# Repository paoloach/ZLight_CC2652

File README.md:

# ZLight_CC2652
A light and a PIR handled by Zigbee

The firmware is made for a CC2652RB and CC2652P TI chips and it is avaiable under the firmware folder.
The first version was for E72-2G4M05S1F (CC2652RB) module but for his shortage, I migrated to the E72-2G4M05S1E module, based on CC2652P1F chip.

For licence issue, I can't put the sources, but you can request at me (pachdjian@gmail.com)

Into firmware folder there are both the firmware.
Into Box, there is a Freecad model for a box I made
Into Schematic thare is two versions on a KiCad circuit with a PCB layout. 
 * The first version is for a E72-2G4M05S1F and it is without a PIR connector.
 * The second version is for a E72-2G4M05S1E module, it contains some fixes and enanchements 

# Instruction

The power supply is 12 Volts. The maximum limits is set by the LM1117 chip that has a maximum input value of 15 Volts.
The PIR used is a AS312, but there are a plenty of others PIR sensors. The important thing is that it should be power by 3.3 volt and a digital output.

The consume is about 0.4 - 0.5 A, so the maximum  emitted light is about 5-6 Watt.
It implement a On/Off and Controll cluster, so you can reduce the luminosity.

The first time the ZLight start it search for a available network.
The two leds blink alternately.

If you need to reset the network, press button 1 for more that 5 seconds.

Then the ZLight will be reset the network configuration and it will begin to search for a new network, blinking the two leds

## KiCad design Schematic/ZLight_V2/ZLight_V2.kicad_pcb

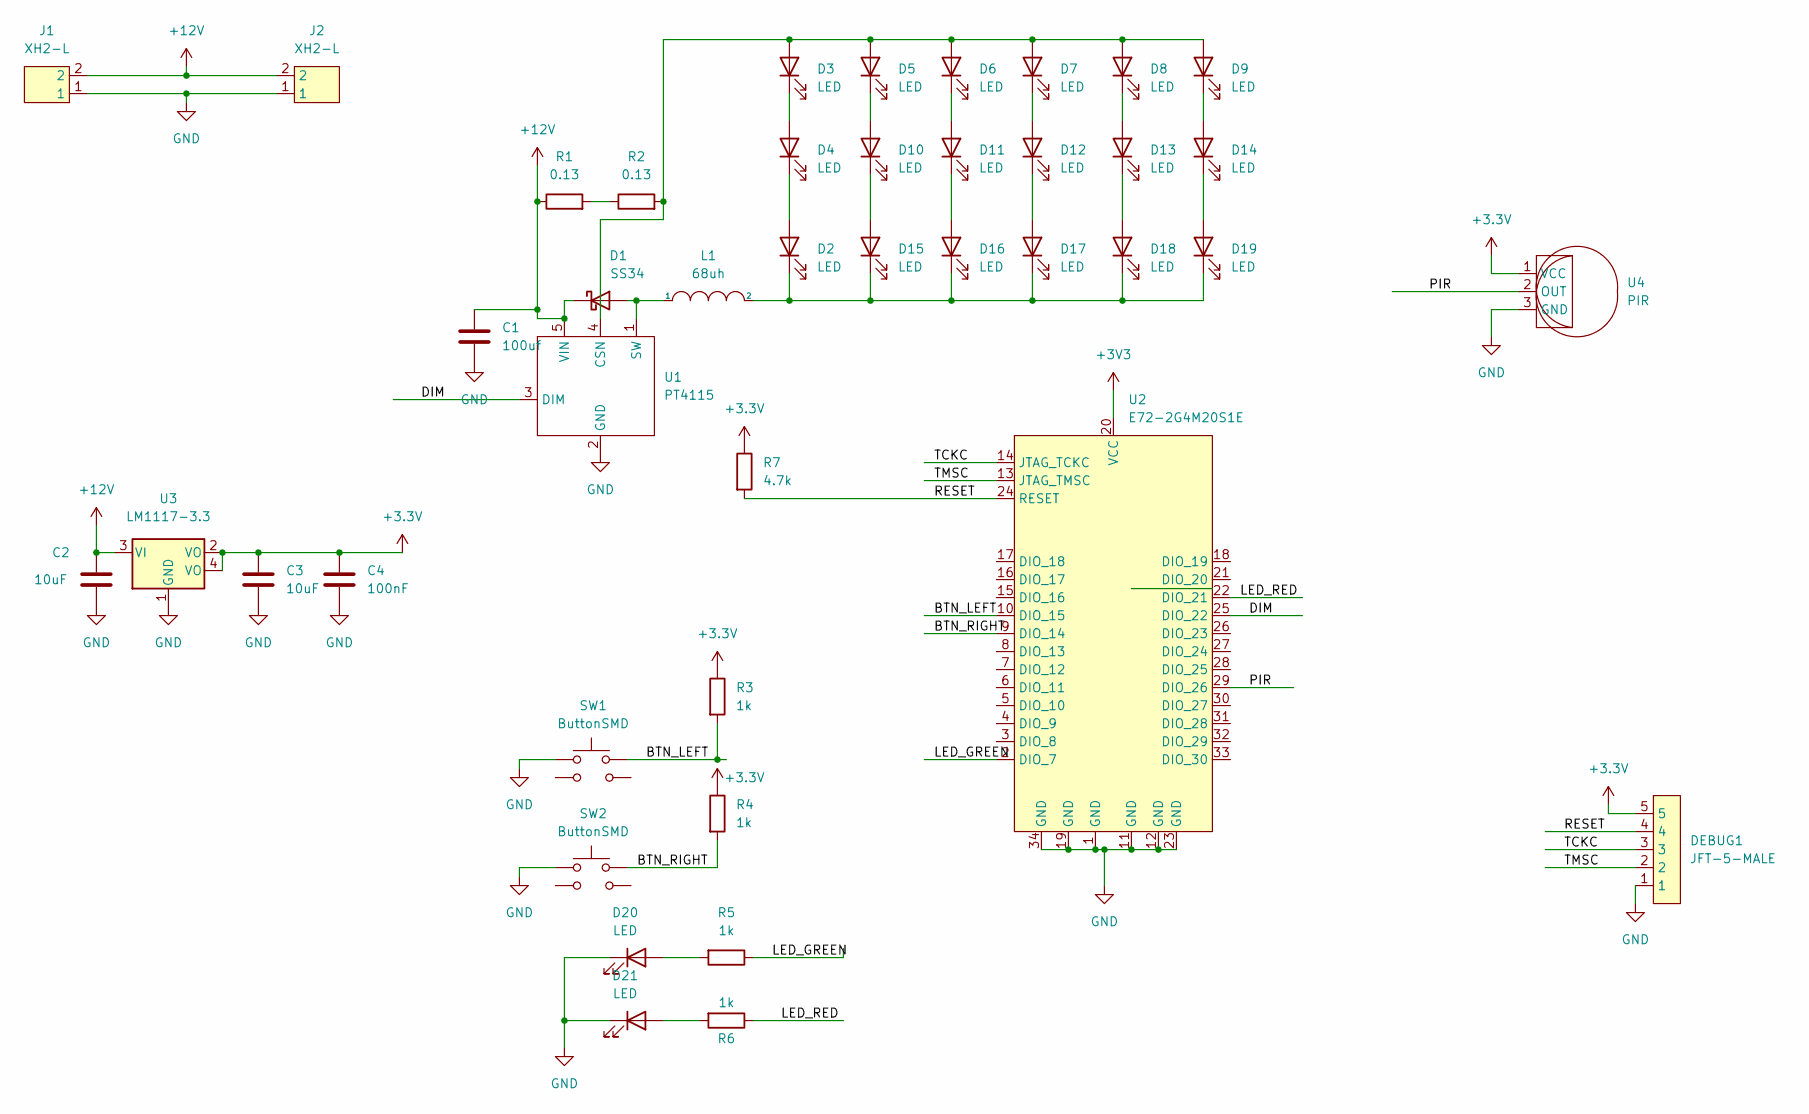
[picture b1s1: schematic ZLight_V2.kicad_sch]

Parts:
C1: 100uf; C_1210_3225Metric_Pad1.33x2.70mm_HandSolder
C2, C3: 10uF; C_0603_1608Metric_Pad1.08x0.95mm_HandSolder
C4: 100nF; C_0603_1608Metric_Pad1.08x0.95mm_HandSolder
D1: SS34
D2, D3, D4, D5, D6, D7, D8, D9, D10, D11, D12, D13, D14, D15, D16, D17, D18, D19: LED; LED_Yuji_5730
D20, D21: LED; LED_0603_1608Metric_Pad1.05x0.95mm_HandSolder
DEBUG1: JFT-5-MALE; XH5-V
J1, J2: XH2-L; XH2-H
L1: 68uh; RH127
R1, R2: 0.13; R_0603_1608Metric_Pad0.98x0.95mm_HandSolder
R3, R4, R5, R6: 1k; R_0603_1608Metric_Pad0.98x0.95mm_HandSolder
R7: 4.7k; R_0603_1608Metric_Pad0.98x0.95mm_HandSolder
SW1, SW2: ButtonSMD
U1: PT4115; SOT-89-5_Handsoldering
U2: E72-2G4M20S1E
U3: LM1117-3.3; SOT-223
U4: PIR; XH3-V

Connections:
+12V: C1.1, C2.1, D1.1 (K), J1.2, J2.2, R1.1, U1.5 (VIN), U3.3 (VI)
/BTN_LEFT: R3.2, SW1.2, U2.10 (DIO_15)
/BTN_RIGHT: R4.2, SW2.2, U2.9 (DIO_14)
/DIM: U1.3 (DIM), U2.25 (DIO_22)
/LED_GREEN: R5.1, U2.2 (DIO_7)
/LED_RED: R6.1, U2.22 (DIO_21)
/PIR: U2.29 (DIO_26), U4.2 (OUT)
/RESET: DEBUG1.4, R7.2, U2.24 (RESET)
/TCKC: DEBUG1.3, U2.14 (JTAG_TCKC)
/TMSC: DEBUG1.2, U2.13 (JTAG_TMSC)
GND: C1.2, C2.2, C3.2, C4.2, D20.1 (K), D21.1 (K), DEBUG1.1, J1.1, J2.1, SW1.1, SW2.1, U1.2 (GND), U2.1 (GND), U2.11 (GND), U2.12 (GND), U2.19 (GND), U2.23 (GND), U2.34 (GND), U3.1 (GND), U4.3 (GND)
unnamed: D1.2 (A), L1.1, U1.1 (SW)
unnamed: D2.2 (A), D4.1 (K)
unnamed: D3.1 (K), D4.2 (A)
unnamed: D3.2 (A), D5.2 (A), D6.2 (A), D7.2 (A), D8.2 (A), D9.2 (A), R2.2, U1.4 (CSN)
unnamed: D10.1 (K), D15.2 (A)
unnamed: D5.1 (K), D10.2 (A)
unnamed: D11.1 (K), D16.2 (A)
unnamed: D6.1 (K), D11.2 (A)
unnamed: D12.1 (K), D17.2 (A)
unnamed: D7.1 (K), D12.2 (A)
unnamed: D13.1 (K), D18.2 (A)
unnamed: D8.1 (K), D13.2 (A)
unnamed: D14.1 (K), D19.2 (A)
unnamed: D9.1 (K), D14.2 (A)
unnamed: D2.1 (K), D15.1 (K), D16.1 (K), D17.1 (K), D18.1 (K), D19.1 (K), L1.2
unnamed: D20.2 (A), R5.2
unnamed: D21.2 (A), R6.2
unnamed: R1.2, R2.1

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
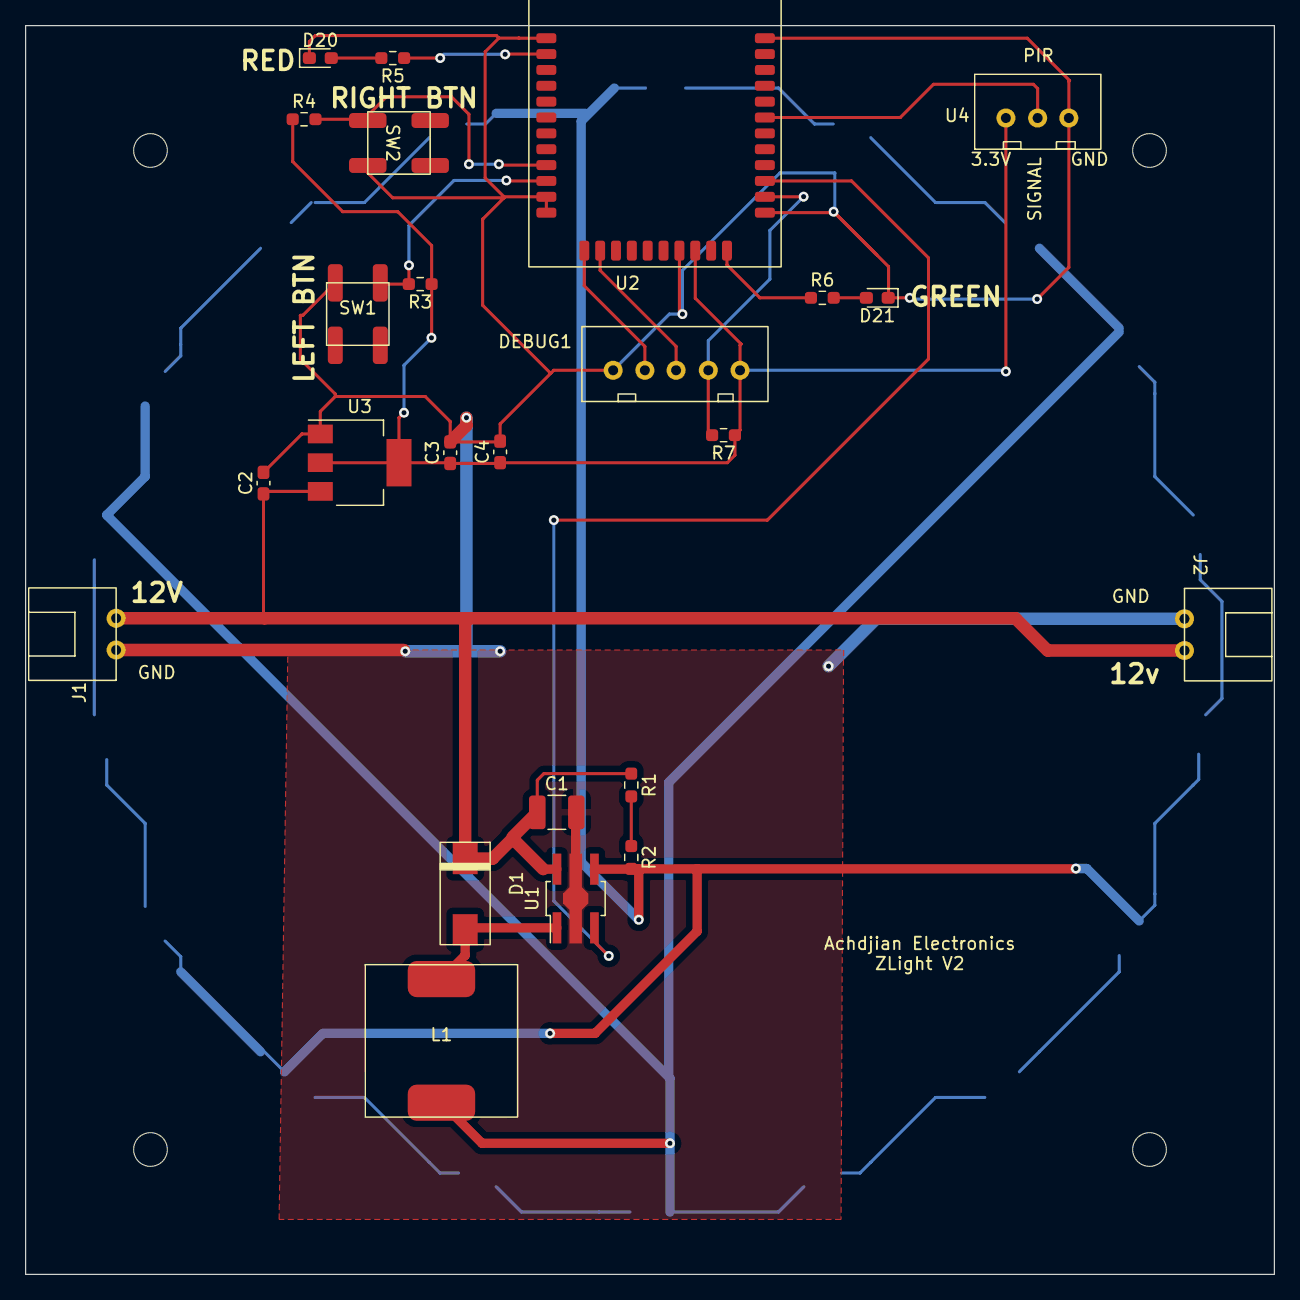
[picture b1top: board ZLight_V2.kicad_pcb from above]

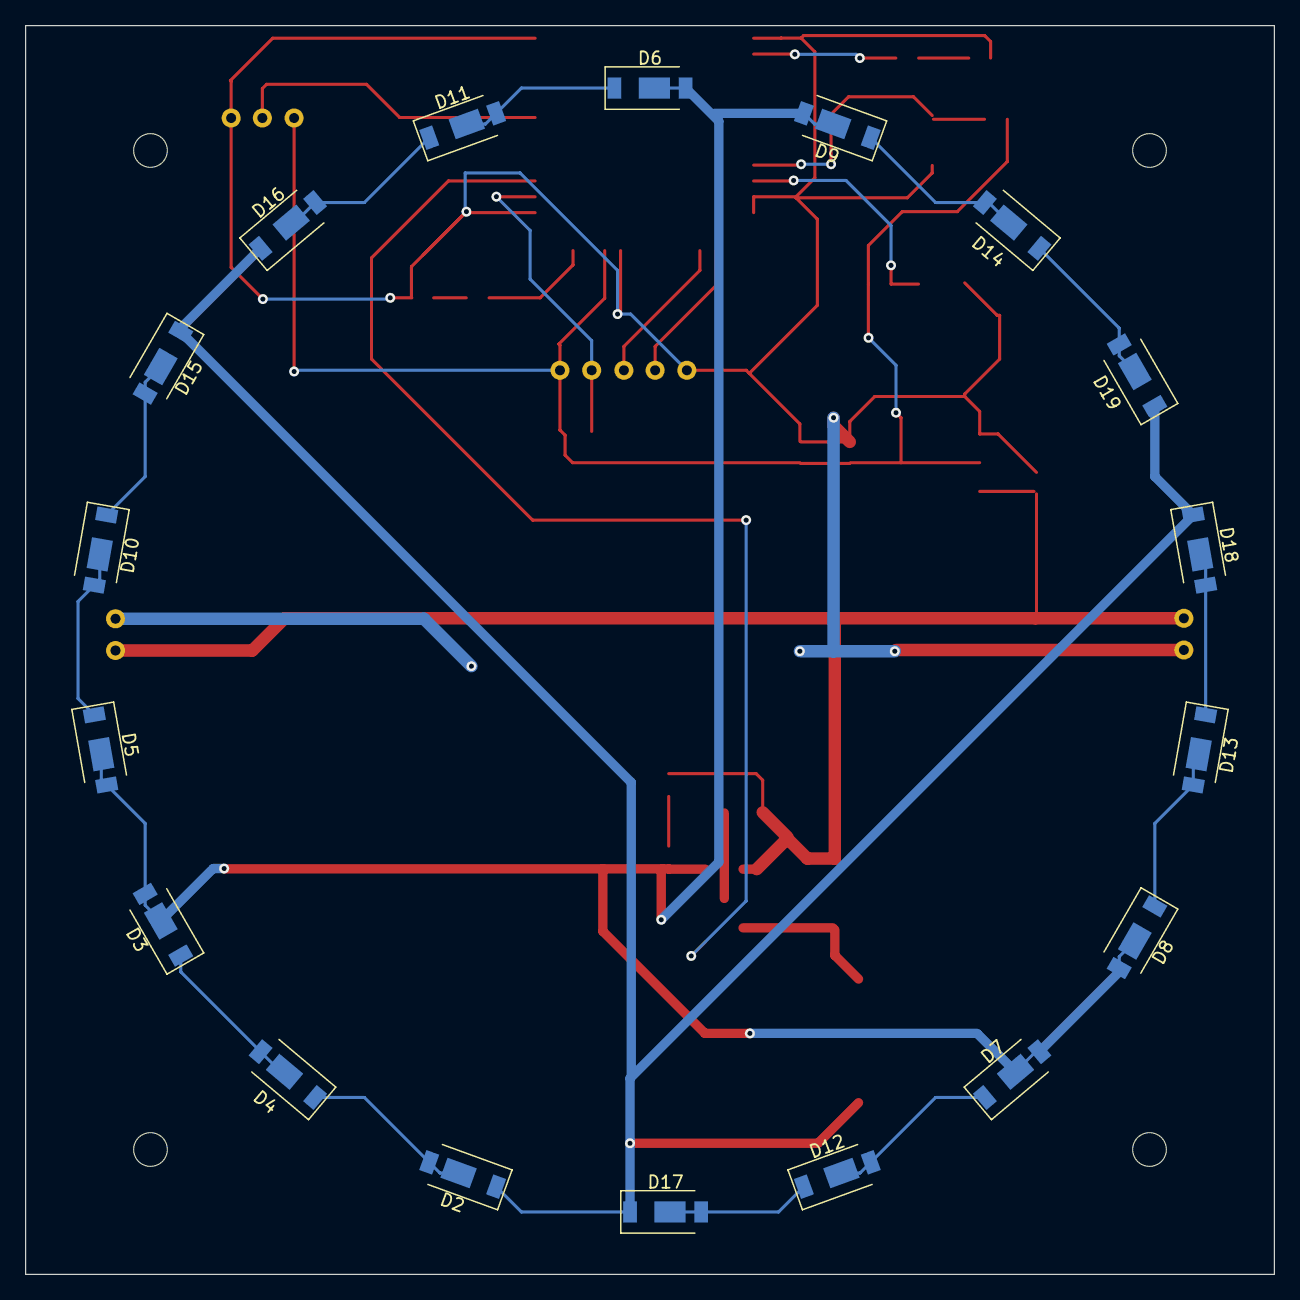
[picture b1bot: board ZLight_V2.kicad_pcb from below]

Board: 2 copper layers, 100.0 x 100.0 mm, 42 parts (18 on the bottom side), 30 nets.

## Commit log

2022-11-27 Add freecad box and cc2652P1F PCB version
2022-11-29 Update readme and add CC2652P1F firmware
